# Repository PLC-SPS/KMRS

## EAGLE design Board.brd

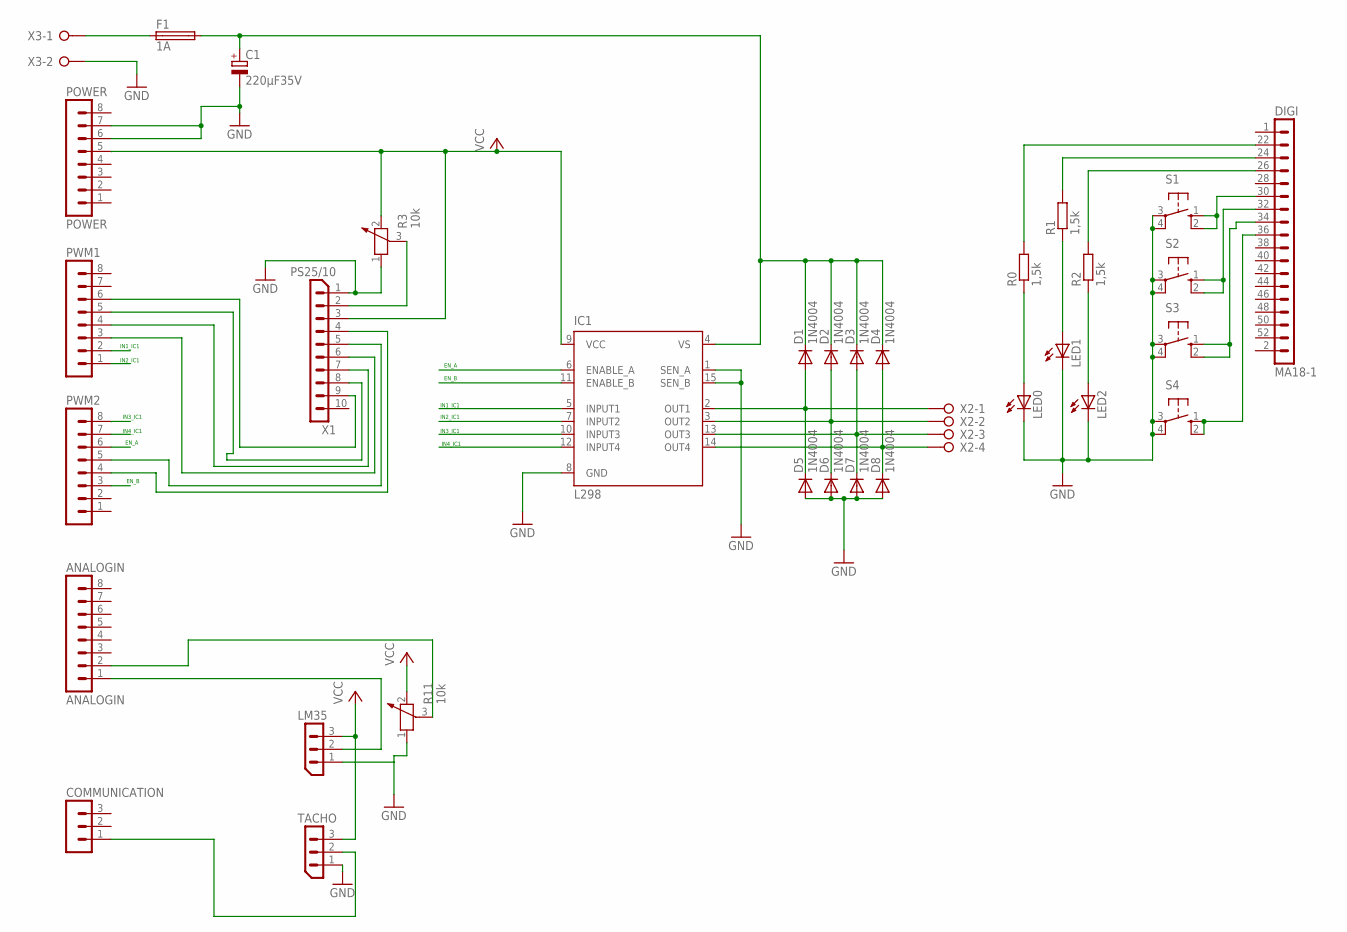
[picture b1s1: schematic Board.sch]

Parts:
ANALOGIN: ANALOGIN; MA08-1
C1: 220µF35V; E5-10,5
COMMUNICATION: MA03-1
D1, D2, D3, D4, D5, D6, D7, D8: 1N4004; DO41-10
DIGI: MA18-1
F1: 1A; 19560
IC1: L298; MULTIWATT-15
LED0, LED1, LED2: LED3MM
LM35: PS25/10
POWER: POWER; MA08-1
PWM1, PWM2: MA08-1
R0, R1, R2: 1,5k; 0207/10
R3, R11: 10k; PT-10
S1, S2, S3, S4: 10-XX; B3F-10XX
TACHO: PS25/10
X1: PS25/10
X2: W237-04P; W237-4P
X3: W237-02P; W237-132

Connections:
EN_A: IC1.6 (ENABLE_A), PWM2.6
EN_B: IC1.11 (ENABLE_B), PWM2.3
GND: C1.-, D5.A, D6.A, D7.A, D8.A, IC1.1 (SEN_A), IC1.8 (GND), IC1.15 (SEN_B), LED0.K (C), LED1.K (C), LED2.K (C), LM35.1, POWER.6, POWER.7, R3.1, R11.1, S1.3, S1.4 (P1), S2.3, S2.4 (P1), S3.3, S3.4 (P1), S4.3, S4.4 (P1), TACHO.1, X1.1, X3.2
IN1_IC1: IC1.5 (INPUT1), PWM1.2
IN2_IC1: IC1.7 (INPUT2), PWM1.1
IN3_IC1: IC1.10 (INPUT3), PWM2.8
IN4_IC1: IC1.12 (INPUT4), PWM2.7
unnamed: COMMUNICATION.1, TACHO.2
unnamed: PWM1.6, X1.9
unnamed: ANALOGIN.2, R11.3
unnamed: PWM1.5, X1.8
unnamed: PWM1.4, X1.7
unnamed: PWM1.3, X1.6
unnamed: PWM2.5, X1.5
unnamed: PWM2.4, X1.4
unnamed: R3.3, X1.2
unnamed: F1.1, X3.1
unnamed: C1.+, D1.C, D2.C, D3.C, D4.C, F1.2, IC1.4 (VS)
unnamed: LED0.A, R0.1
unnamed: DIGI.24, R1.2
unnamed: LED1.A, R1.1
unnamed: D4.A, D8.C, IC1.14 (OUT4), X2.4
unnamed: DIGI.22, R0.2
unnamed: LED2.A, R2.1
unnamed: DIGI.26, R2.2
unnamed: DIGI.36, S4.1 (S), S4.2 (S1)
unnamed: DIGI.34, S3.1 (S), S3.2 (S1)
unnamed: DIGI.32, S2.1 (S), S2.2 (S1)
unnamed: DIGI.30, S1.1 (S), S1.2 (S1)
unnamed: D1.A, D5.C, IC1.2 (OUT1), X2.1
unnamed: D2.A, D6.C, IC1.3 (OUT2), X2.2
unnamed: D3.A, D7.C, IC1.13 (OUT3), X2.3
RASTER: ANALOGIN.1, LM35.2
VCC: IC1.9 (VCC), LM35.3, POWER.5, R3.2, R11.2, TACHO.3, X1.3

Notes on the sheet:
IN1_IC1
IN2_IC1
IN3_IC1
IN4_IC1
EN_A
EN_B

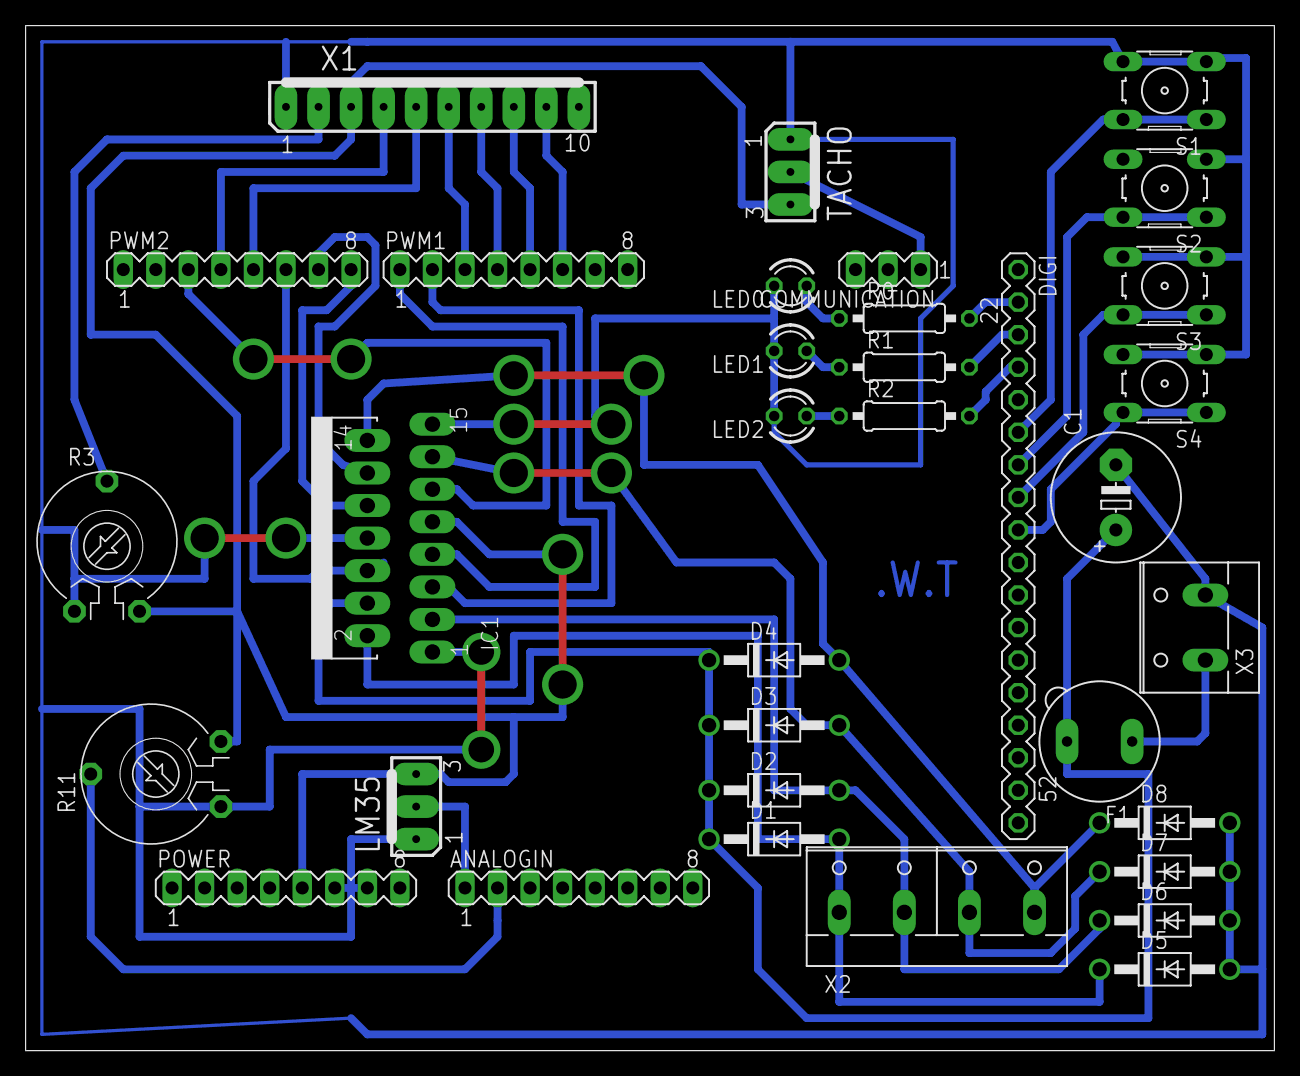
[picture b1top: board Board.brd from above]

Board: 2 copper layers, 97.5 x 80.0 mm, 34 parts (0 on the bottom side), 34 nets.
